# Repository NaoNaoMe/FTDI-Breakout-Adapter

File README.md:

FTDI Breakout Adapter
=========

The FTDI Breakout Adapter convert interface from the FTDI Basic Breakout board pin-out to XH connector.
It is used for flashing software in [Uart WiFi Board](https://github.com/NaoNaoMe/Uart-WiFi-Board).

Repository Contents
-------------------
* **/Hardware** - All Eagle design files (.brd, .sch)
* **/Cables** - Cables info

Description(Pin Interfaces)
-------------------

### CN1 Pin Descriptions:
This headers are for an FTDI port.

### CN2 Pin Descriptions:
This connector is for your target board.

| Pin | Name | Description                                       |
| --- | ---- | ------------------------------------------------- |
| 1   | VCC  | VCC-CN1 with a jumper (Short or Open)             |
| 2   | TX   | TXD-CN1                                           |
| 3   | -    | No connection.                                    |
| 4   | RX   | RXD-CN1                                           |
| 5   | GND  | GND-CN1                                           |
| 6   | I/S  | CTS-CN1 with a jumper (High, Low or No-connect)   |
| 7   | OUT  | DTR/RTS-CN1                                       |

### Jumpers:
 - **JP1:** This jumper changes the voltage level on CN2-I/S pin.
 - **JP2:** This jumper allows you to supply voltage from FTDI port.

License
-------------------
The repository is released under [Creative Commons ShareAlike 4.0 International](https://creativecommons.org/licenses/by-sa/4.0/).

Distributed as-is; no warranty is given.

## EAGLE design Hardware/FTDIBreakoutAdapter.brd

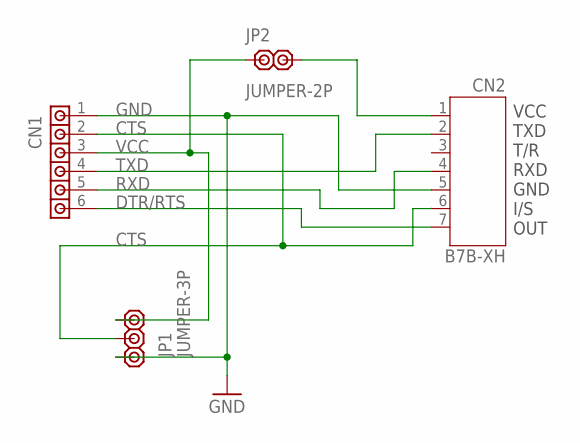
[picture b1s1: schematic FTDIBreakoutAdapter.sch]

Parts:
CN1: H6-2.54-90D-MALE
CN2: B7B-XH
JP1: JUMPER-3P
JP2: JUMPER-2P

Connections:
CTS: CN1.2, CN2.6, JP1.2
DTR/RTS: CN1.6, CN2.7
GND: CN1.1, CN2.5, JP1.3
unnamed: CN2.1, JP2.2
RXD: CN1.5, CN2.4
TXD: CN1.4, CN2.2
VCC: CN1.3, JP1.1, JP2.1

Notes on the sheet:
VCC TXD T/R RXD GND I/S OUT

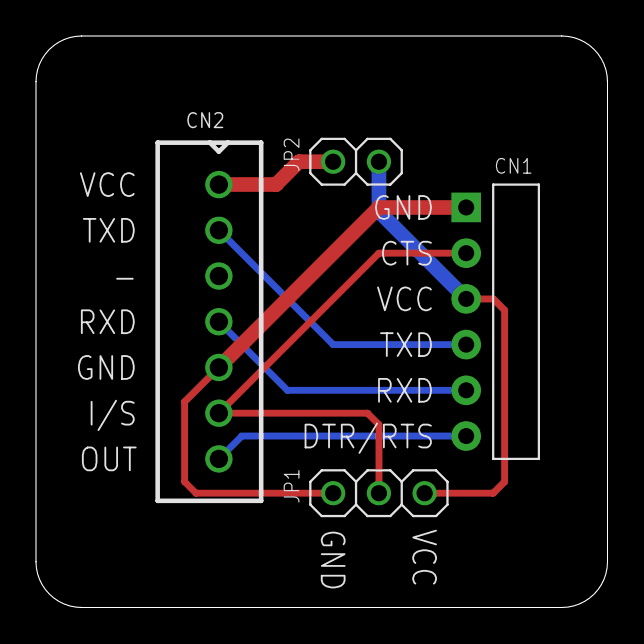
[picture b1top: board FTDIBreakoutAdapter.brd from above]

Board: 2 copper layers, 31.8 x 31.8 mm, 4 parts (0 on the bottom side), 7 nets.

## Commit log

2018-04-18 Upload files
2018-04-18 Fix Readme
2018-04-18 Fix cables info

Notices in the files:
parts and their libraries:
jst: Copyright (C) 2016, Naoya Imai
